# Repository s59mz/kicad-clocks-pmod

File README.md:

# clocks_pmod
PMOD PCB module for Si5351 and CJMCU-9833 Clock Synchronizer modules 

Schematic:
[clocks_pmod.pdf](https://github.com/s59mz/kicad-clocks-pmod/raw/main/clocks_pmod.pdf)

BOM:
[clocks_pmod.csv](clocks_pmod.csv)

Gerbers:
[gerbers.zip](https://github.com/s59mz/kicad-clocks-pmod/raw/main/gerbers.zip)

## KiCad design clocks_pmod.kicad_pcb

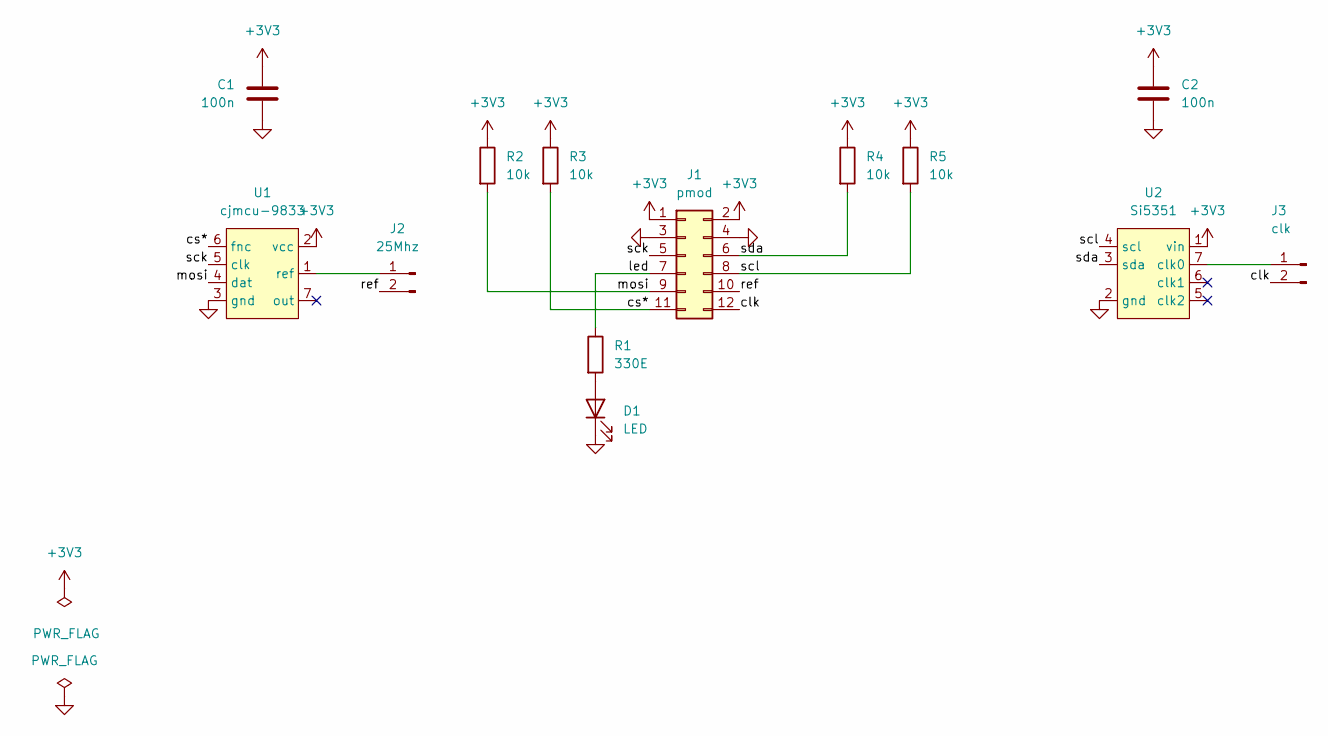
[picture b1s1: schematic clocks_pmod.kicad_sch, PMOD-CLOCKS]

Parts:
C1, C2: 100n; C_0603_1608Metric_Pad1.08x0.95mm_HandSolder
D1: LED; LED_0603_1608Metric_Pad1.05x0.95mm_HandSolder
J1: pmod; PinHeader_2x06_P2.54mm_Horizontal
J2: 25Mhz; PinHeader_1x02_P2.54mm_Vertical
J3: clk; PinHeader_1x02_P2.54mm_Vertical
R1: 330E; R_0603_1608Metric_Pad0.98x0.95mm_HandSolder
R2, R3, R4, R5: 10k; R_0603_1608Metric_Pad0.98x0.95mm_HandSolder
U1: cjmcu-9833
U2: Si5351

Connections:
+3V3: C1.1, C2.1, J1.1, J1.2, R2.1, R3.1, R4.1, R5.1, U1.2 (vcc), U2.1 (vin)
/clk: J1.12, J3.2
/cs*: J1.11, R3.2, U1.6 (fnc)
/led: J1.7, R1.1
/mosi: J1.9, R2.2, U1.4 (dat)
/ref: J1.10, J2.2
/sck: J1.5, U1.5 (clk)
/scl: J1.8, R5.2, U2.4 (scl)
/sda: J1.6, R4.2, U2.3 (sda)
GND: C1.2, C2.2, D1.1 (K), J1.3, J1.4, U1.3 (gnd), U2.2 (gnd)
unnamed: D1.2 (A), R1.2
unnamed: J2.1, U1.1 (ref)
unnamed: J3.1, U2.7 (clk0)

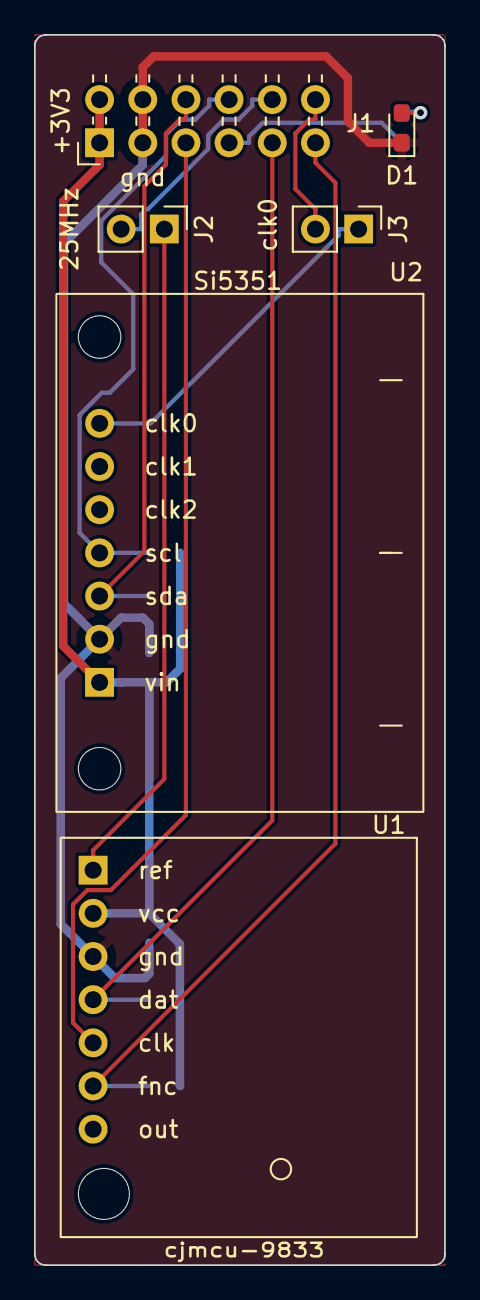
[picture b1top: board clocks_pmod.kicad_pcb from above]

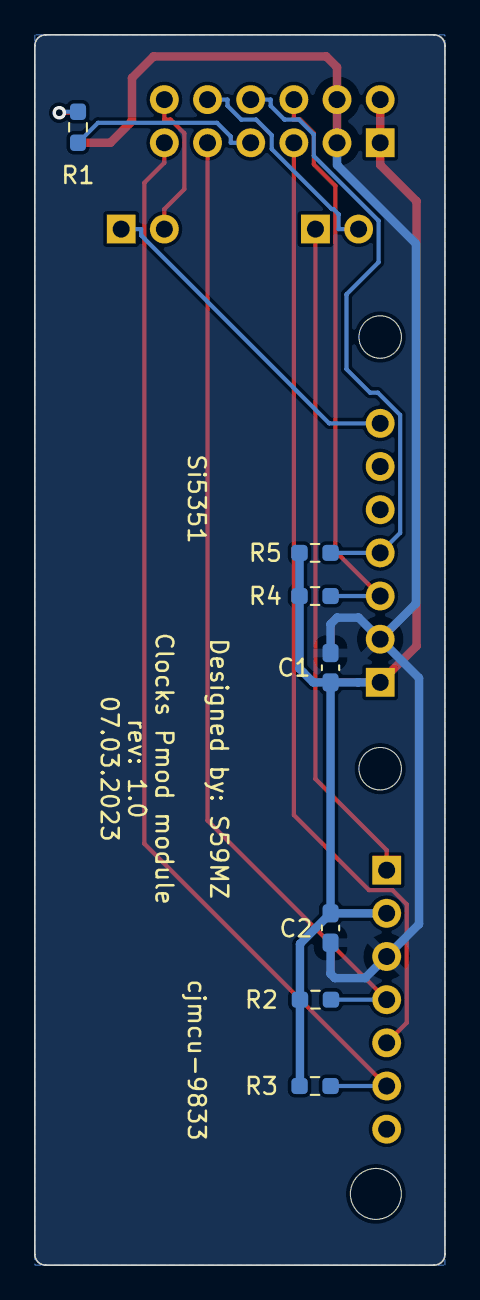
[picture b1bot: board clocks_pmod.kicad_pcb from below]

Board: 2 copper layers, 24.1 x 72.4 mm, 13 parts (7 on the bottom side), 13 nets.

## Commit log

2024-08-11 Add screeenshots
2024-08-11 updated bom
